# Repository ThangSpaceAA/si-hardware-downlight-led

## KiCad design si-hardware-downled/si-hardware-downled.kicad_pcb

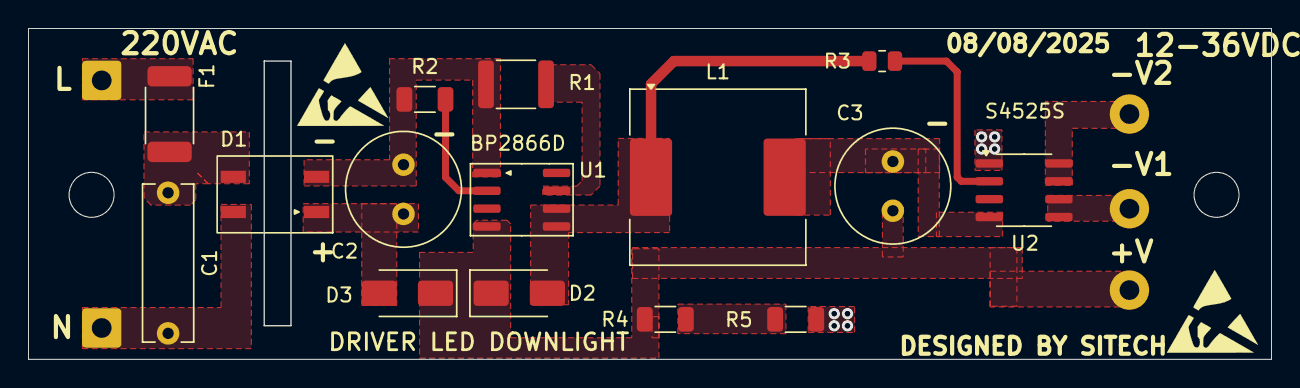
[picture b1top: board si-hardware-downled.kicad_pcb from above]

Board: 2 copper layers, 88.3 x 23.5 mm, 17 parts (0 on the bottom side), 14 nets.

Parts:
C1: 0.1uF/250V; C_Rect_L11.0mm_W3.4mm_P10.00mm_MKT
C2, C3: 4.7uF/400V; C_Radial_D8.0mm_H11.5mm_P3.50mm
D1: MB10F-13; DiodeBridge_MB10F-13
D2, D3: ES1J/1A-600V; D_SMA
F1: 500mA/250VAC; Fuse_1808_4532Metric
H1, H2: MountingHole_Pad_MP; MountingHole_3.2mm_M3_DIN965_Pad
L1: 1mH/1A; L_Coilcraft_MSS1210H-XXX
R1: 1R-1%; R_1812_4532Metric
R2: 18K; R_1206_3216Metric
R3: 330K; R_0805_2012Metric
R4, R5: 27K; R_1206_3216Metric
U1: BP2866D; BP2866
U2: S4525S; SOIC-8_3.9x4.9mm_P1.27mm

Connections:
GND: C2.2, D1.3 (-), R1.2, R2.2, U1.1 (GND)
GND1: C3.2, L1.2, U2.4 (GND)
LINE: C1.1, D1.4, F1.2
NEUT: C1.2, D1.2
unnamed: C2.1, D1.1 (+), D3.2 (A)
unnamed: D2.2 (A), L1.1, R3.1, U1.5 (DRAIN), U1.6 (DRAIN)
unnamed: R4.1, R5.2
unnamed: R1.1, U1.7 (CS)
unnamed: R2.1, U1.2 (ROVP)
unnamed: R3.2, U2.2 (CLK)
unnamed: U2.7 (D1), U2.8 (D1)
unnamed: U2.5 (D2), U2.6 (D2)
unnamed: R5.1, U2.1 (HV)
VCC: C3.1, D2.1 (K), D3.1 (K), R4.2, U1.4 (HV)

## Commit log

2025-08-06 added submodule libraries
2025-08-08 change placement pcb all
2025-08-09 change inductor choke filter
2025-08-12 export file gerber + drill
2025-08-27 change footprint
2025-09-26 final routing and placement
